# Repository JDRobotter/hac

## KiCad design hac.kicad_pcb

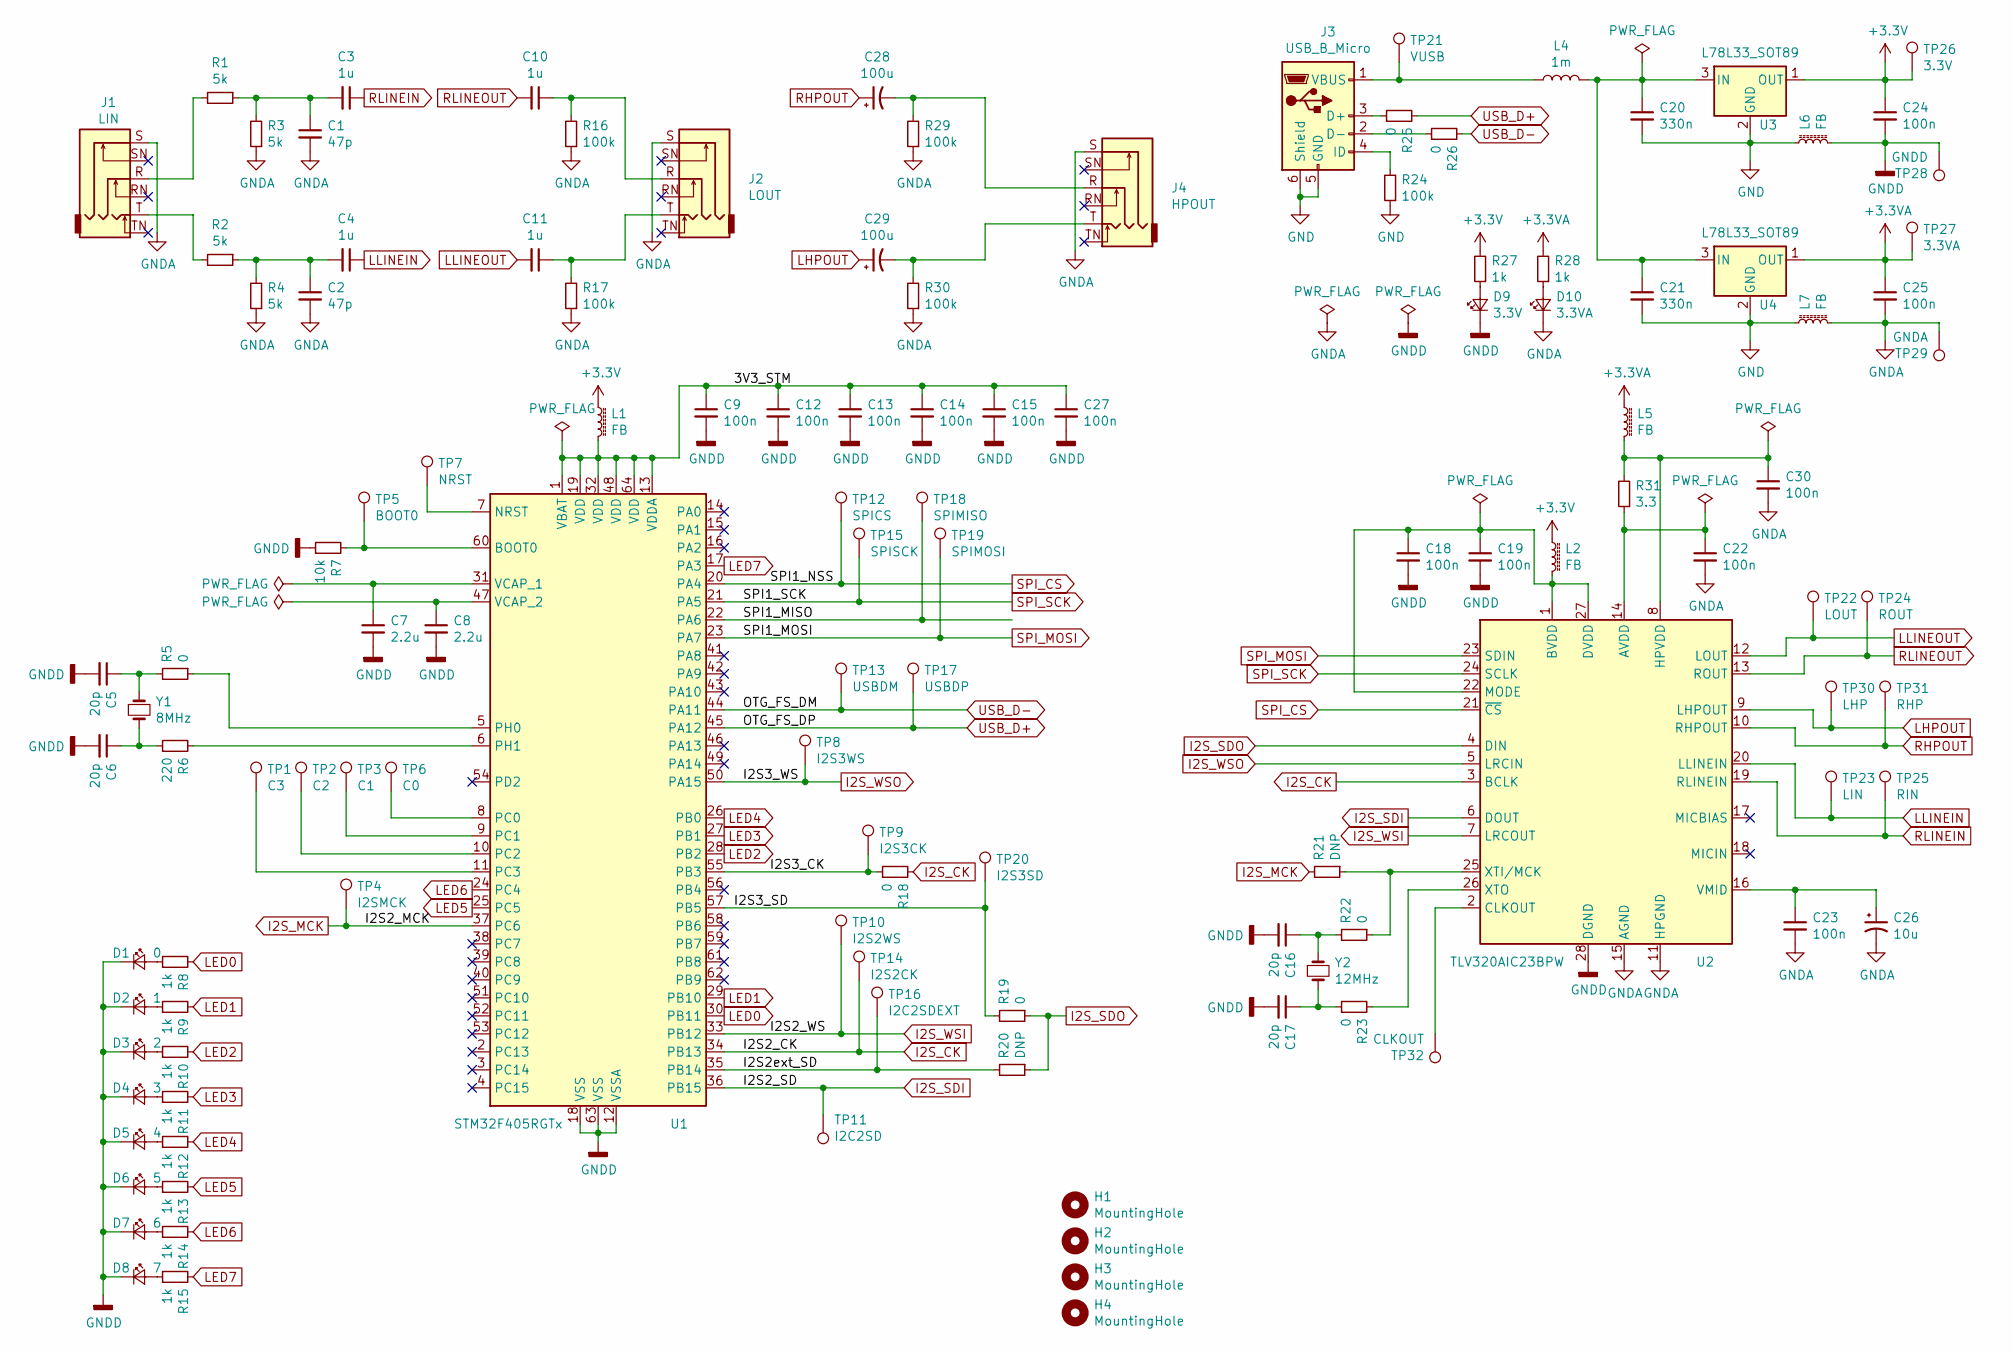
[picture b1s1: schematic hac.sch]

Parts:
C1, C2: 47p; C_0603_1608Metric
C3, C4, C10, C11: 1u; C_0805_2012Metric
C5, C6, C16, C17: 20p; C_0603_1608Metric
C7, C8: 2.2u; C_0805_2012Metric
C9, C12, C13, C14, C15, C18, C19, C22, C23, C24, C25, C27, C30: 100n; C_0603_1608Metric
C20, C21: 330n; C_0603_1608Metric
C26: 10u; CP_EIA-3216-18_Kemet-A
C28, C29: 100u; CP_EIA-6032-28_Kemet-C
D1: 0; LED_0603_1608Metric
D2: 1; LED_0603_1608Metric
D3: 2; LED_0603_1608Metric
D4: 3; LED_0603_1608Metric
D5: 4; LED_0603_1608Metric
D6: 5; LED_0603_1608Metric
D7: 6; LED_0603_1608Metric
D8: 7; LED_0603_1608Metric
D9: 3.3V; LED_0603_1608Metric
D10: 3.3VA; LED_0603_1608Metric
H1, H2, H3, H4: MountingHole; MountingHole_3.2mm_M3
J1: LIN; Jack_3.5mm_Neutrik_NMJ6HCD2_Horizontal
J2: LOUT; Jack_3.5mm_Neutrik_NMJ6HCD2_Horizontal
J3: USB_B_Micro; USB_Micro-B_Molex-105017-0001
J4: HPOUT; Jack_3.5mm_Neutrik_NMJ6HCD2_Horizontal
L1, L2, L5, L6, L7: FB; L_0805_2012Metric
L4: 1m; L_7.3x7.3_H4.5
R1, R2, R3, R4: 5k; R_0603_1608Metric
R5, R18, R19, R22, R23, R25, R26: 0; R_0603_1608Metric
R6: 220; R_0603_1608Metric
R7: 10k; R_0603_1608Metric
R8, R9, R10, R11, R12, R13, R14, R15, R27, R28: 1k; R_0603_1608Metric
R16, R17, R24, R29, R30: 100k; R_0603_1608Metric
R20, R21: DNP; R_0603_1608Metric
R31: 3.3; R_0603_1608Metric
TP1: C3; TestPoint_Pad_D1.5mm
TP2: C2; TestPoint_Pad_D1.5mm
TP3: C1; TestPoint_Pad_D1.5mm
TP4: I2SMCK; TestPoint_Pad_D1.5mm
TP5: BOOT0; TestPoint_Pad_D1.5mm
TP6: C0; TestPoint_Pad_D1.5mm
TP7: NRST; TestPoint_Pad_D1.5mm
TP8: I2S3WS; TestPoint_Pad_D1.5mm
TP9: I2S3CK; TestPoint_Pad_D1.5mm
TP10: I2S2WS; TestPoint_Pad_D1.5mm
TP11: I2C2SD; TestPoint_Pad_D1.5mm
TP12: SPICS; TestPoint_Pad_D1.5mm
TP13: USBDM; TestPoint_Pad_D1.5mm
TP14: I2S2CK; TestPoint_Pad_D1.5mm
TP15: SPISCK; TestPoint_Pad_D1.5mm
TP16: I2C2SDEXT; TestPoint_Pad_D1.5mm
TP17: USBDP; TestPoint_Pad_D1.5mm
TP18: SPIMISO; TestPoint_Pad_D1.5mm
TP19: SPIMOSI; TestPoint_Pad_D1.5mm
TP20: I2S3SD; TestPoint_Pad_D1.5mm
TP21: VUSB; TestPoint_Pad_D1.5mm
TP22: LOUT; TestPoint_Pad_D1.5mm
TP23: LIN; TestPoint_Pad_D1.5mm
TP24: ROUT; TestPoint_Pad_D1.5mm
TP25: RIN; TestPoint_Pad_D1.5mm
TP26: 3.3V; TestPoint_Pad_D1.5mm
TP27: 3.3VA; TestPoint_Pad_D1.5mm
TP28: GNDD; TestPoint_Pad_D1.5mm
TP29: GNDA; TestPoint_Pad_D1.5mm
TP30: LHP; TestPoint_Pad_D1.5mm
TP31: RHP; TestPoint_Pad_D1.5mm
TP32: CLKOUT; TestPoint_Pad_D1.5mm
U1: STM32F405RGTx; LQFP-64_10x10mm_P0.5mm
U2: TLV320AIC23BPW; TSSOP-28_4.4x9.7mm_P0.65mm
U3, U4: L78L33_SOT89; SOT-89-3
Y1: 8MHz; Crystal_SMD_HC49-SD
Y2: 12MHz; Crystal_SMD_HC49-SD

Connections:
+3.3VA: C25.1, L5.1, R28.2, TP27.1, U4.1 (OUT)
+3V3: C24.1, L1.1, L2.1, R27.2, TP26.1, U3.1 (OUT)
/3V3_STM: C9.1, C12.1, C13.1, C14.1, C15.1, C27.1, L1.2, U1.1 (VBAT), U1.13 (VDDA), U1.19 (VDD), U1.32 (VDD), U1.48 (VDD), U1.64 (VDD)
/I2S2ext_SD: R20.2, TP16.1, U1.35 (PB14)
/I2S3_CK: R18.1, TP9.1, U1.55 (PB3)
/I2S3_SD: R19.2, TP20.1, U1.57 (PB5)
/SPI1_MISO: TP18.1, U1.22 (PA6)
GND: C20.2, C21.2, J3.5 (GND), J3.6 (Shield), L6.1, L7.1, R24.1, U3.2 (GND), U4.2 (GND); also elsewhere on the board
GNDA: C1.2, C2.2, C22.2, C23.2, C25.2, C26.2, C30.2, D10.1 (K), J1.S, J2.S, J4.S, L7.2, R3.1, R4.1, R16.1, R17.1, R29.1, R30.1, TP29.1, U2.11 (HPGND), U2.15 (AGND); also elsewhere on the board
GNDD: C5.2, C6.2, C7.2, C8.2, C9.2, C12.2, C13.2, C14.2, C15.2, C16.2, C17.2, C18.2, C19.2, C24.2, C27.2, D1.1 (K), D2.1 (K), D3.1 (K), D4.1 (K), D5.1 (K), D6.1 (K), D7.1 (K), D8.1 (K), D9.1 (K), L6.2, R7.1, TP28.1, U1.12 (VSSA), U1.18 (VSS), U1.63 (VSS), U2.28 (DGND); also elsewhere on the board
I2S_CK: R18.2, TP14.1, U1.34 (PB13), U2.3 (BCLK)
I2S_MCK: R21.2, TP4.1, U1.37 (PC6)
I2S_SDI: TP11.1, U1.36 (PB15), U2.6 (DOUT)
I2S_SDO: R19.1, R20.1, U2.4 (DIN)
I2S_WSI: TP10.1, U1.33 (PB12), U2.7 (LRCOUT)
I2S_WSO: TP8.1, U1.50 (PA15), U2.5 (LRCIN)
LED0: R8.2, U1.30 (PB11)
LED1: R9.2, U1.29 (PB10)
LED2: R10.2, U1.28 (PB2)
LED3: R11.2, U1.27 (PB1)
LED4: R12.2, U1.26 (PB0)
LED5: R13.2, U1.25 (PC5)
LED6: R14.2, U1.24 (PC4)
LED7: R15.2, U1.17 (PA3)
LHPOUT: C29.1, TP30.1, U2.9 (LHPOUT)
LLINEIN: C4.1, TP23.1, U2.20 (LLINEIN)
LLINEOUT: C11.2, TP22.1, U2.12 (LOUT)
unnamed: C1.1, C3.2, R1.1, R3.2
unnamed: C2.1, C4.2, R2.1, R4.2
unnamed: C5.1, R5.2, Y1.1
unnamed: C6.1, R6.1, Y1.2
unnamed: C7.1, U1.31 (VCAP_1)
unnamed: C8.1, U1.47 (VCAP_2)
unnamed: C10.1, J2.R, R16.2
unnamed: C11.1, J2.T, R17.2
unnamed: C16.1, R22.2, Y2.1
unnamed: C17.1, R23.1, Y2.2
unnamed: C18.1, C19.1, L2.2, U2.1 (BVDD), U2.22 (MODE), U2.27 (DVDD)
unnamed: C20.1, C21.1, L4.2, U3.3 (IN), U4.3 (IN)
unnamed: C22.1, R31.1, U2.14 (AVDD)
unnamed: C23.1, C26.1, U2.16 (VMID)
unnamed: C28.2, J4.R, R29.2
unnamed: C29.2, J4.T, R30.2
unnamed: C30.1, L5.2, R31.2, U2.8 (HPVDD)
unnamed: D1.2 (A), R8.1
unnamed: D2.2 (A), R9.1
unnamed: D3.2 (A), R10.1
unnamed: D4.2 (A), R11.1
unnamed: D5.2 (A), R12.1
unnamed: D6.2 (A), R13.1
unnamed: D7.2 (A), R14.1
unnamed: D8.2 (A), R15.1
unnamed: D9.2 (A), R27.1
unnamed: D10.2 (A), R28.1
unnamed: J1.R, R1.2
unnamed: J1.T, R2.2
unnamed: J3.1 (VBUS), L4.1, TP21.1
unnamed: J3.2 (D-), R26.1
unnamed: J3.3 (D+), R25.1
unnamed: J3.4 (ID), R24.2
unnamed: R5.1, U1.5 (PH0)
unnamed: R6.2, U1.6 (PH1)
unnamed: R7.2, TP5.1, U1.60 (BOOT0)
unnamed: R21.1, R22.1, U2.25 (XTI/MCK)
unnamed: R23.2, U2.26 (XTO)
unnamed: TP1.1, U1.11 (PC3)
unnamed: TP2.1, U1.10 (PC2)
unnamed: TP3.1, U1.9 (PC1)
unnamed: TP6.1, U1.8 (PC0)
unnamed: TP7.1, U1.7 (NRST)
unnamed: TP32.1, U2.2 (CLKOUT)
RHPOUT: C28.1, TP31.1, U2.10 (RHPOUT)
RLINEIN: C3.1, TP25.1, U2.19 (RLINEIN)
RLINEOUT: C10.2, TP24.1, U2.13 (ROUT)
SPI_CS: TP12.1, U1.20 (PA4), U2.21 (~CS~)
SPI_MOSI: TP19.1, U1.23 (PA7), U2.23 (SDIN)
SPI_SCK: TP15.1, U1.21 (PA5), U2.24 (SCLK)
USB_D+: R25.2, TP17.1, U1.45 (PA12)
USB_D-: R26.2, TP13.1, U1.44 (PA11)

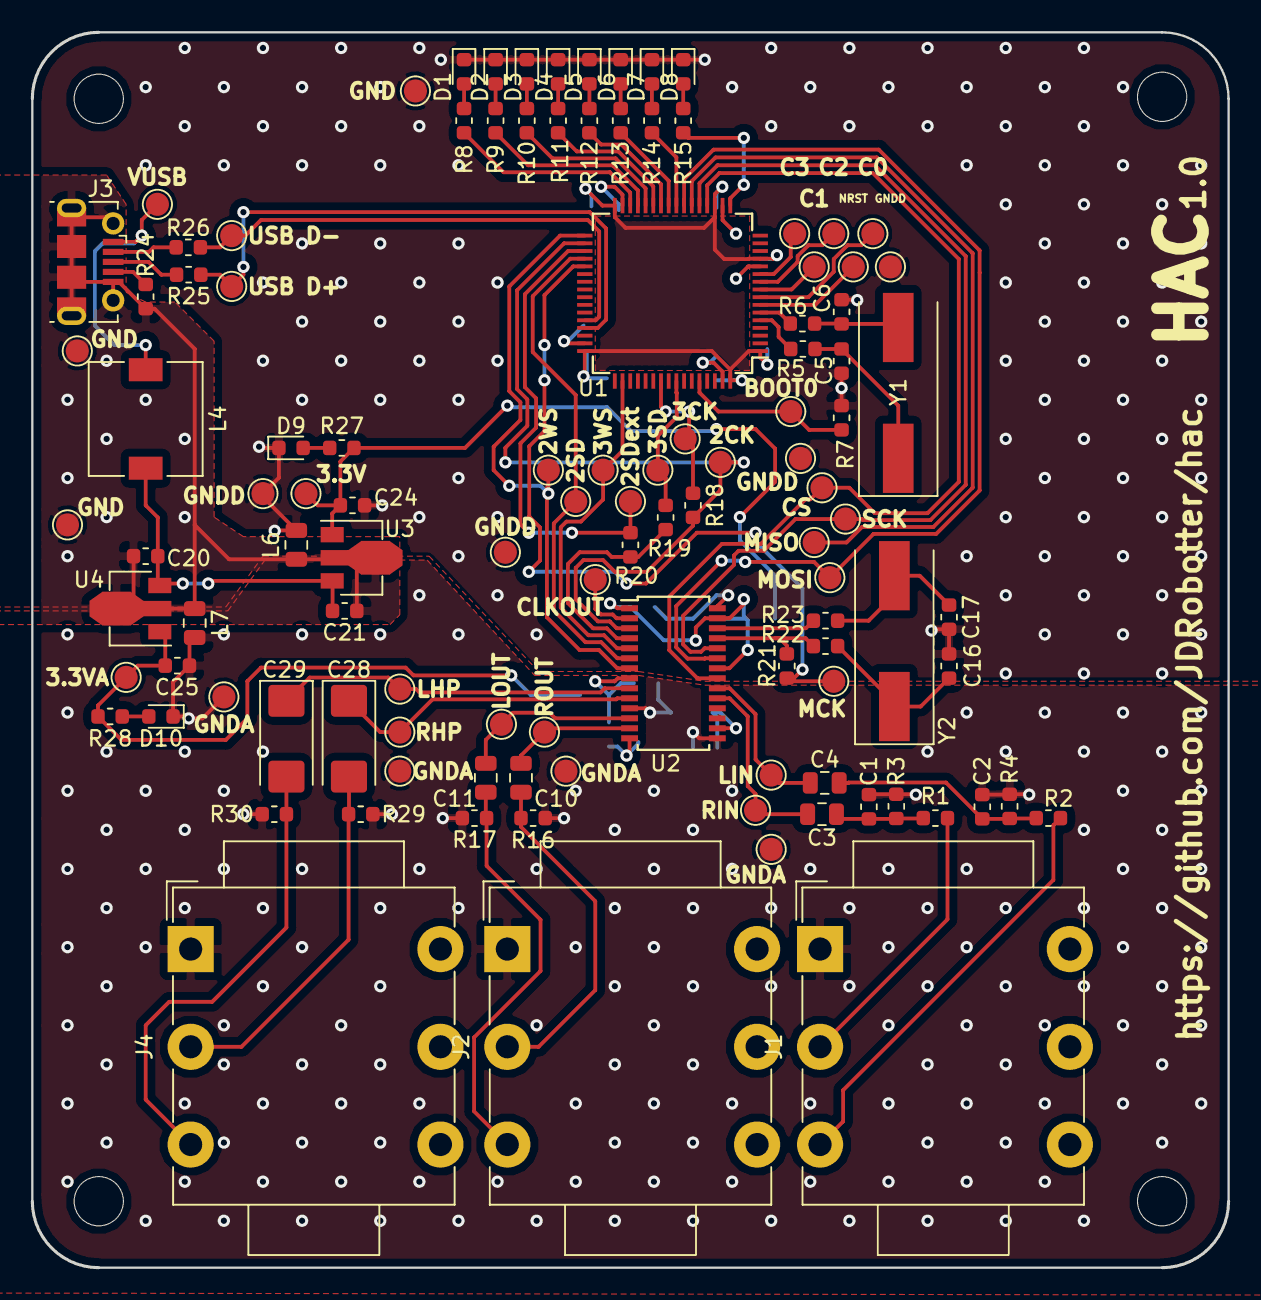
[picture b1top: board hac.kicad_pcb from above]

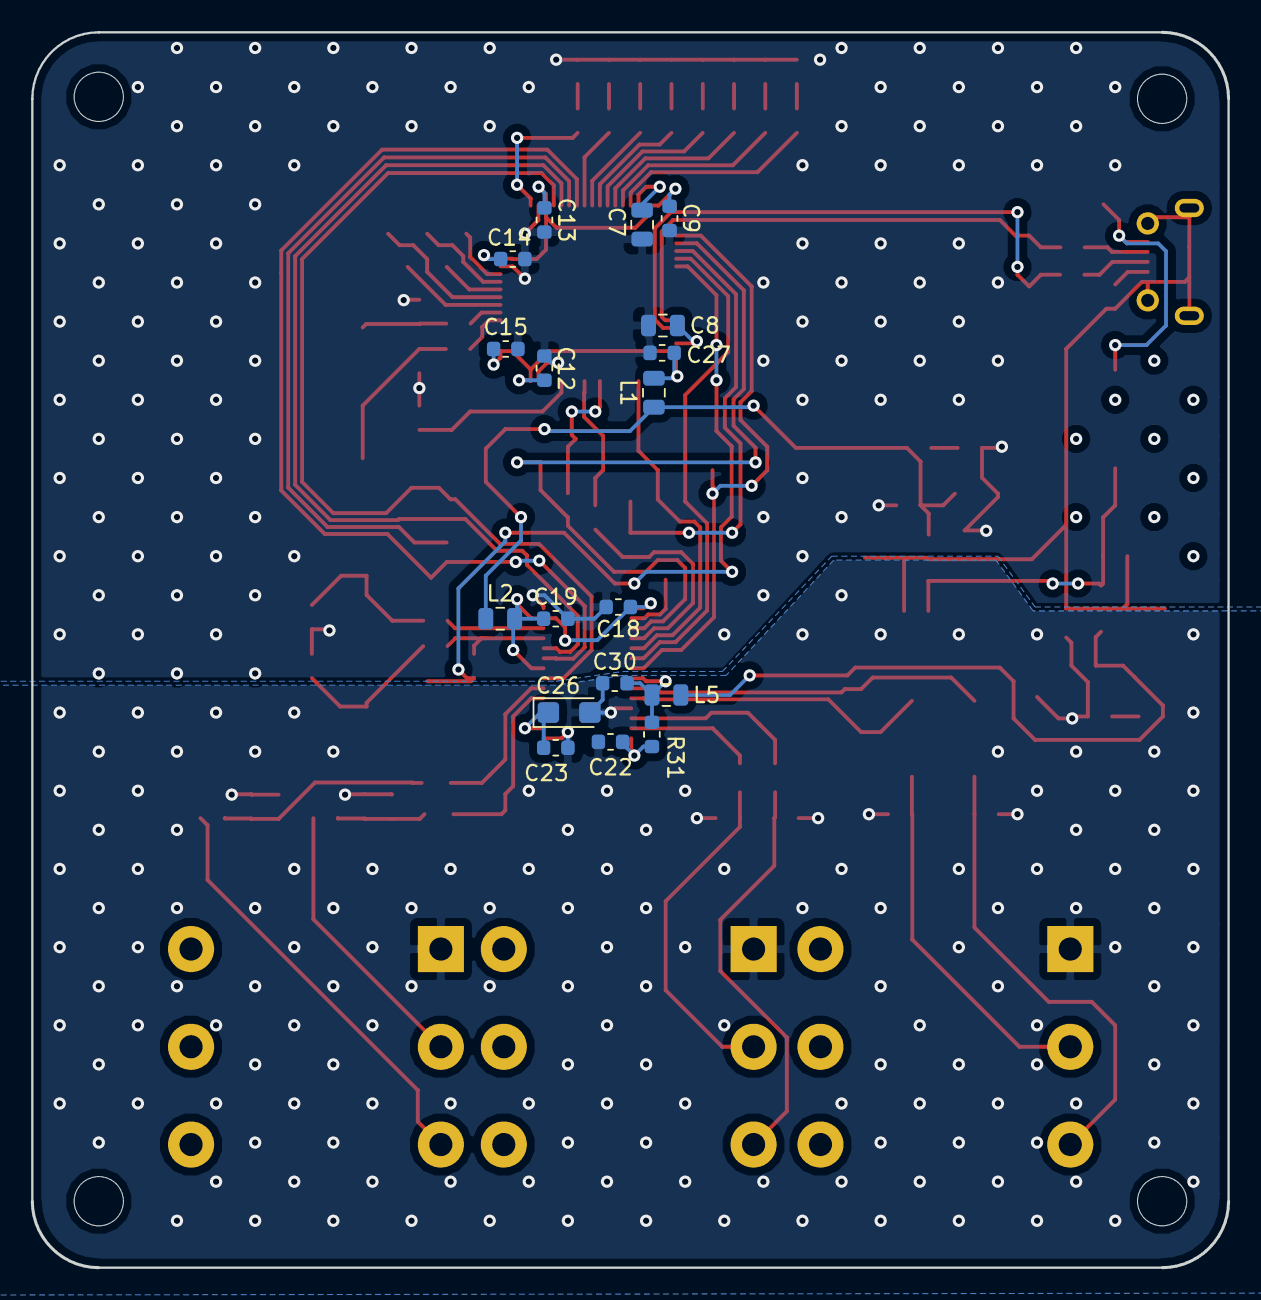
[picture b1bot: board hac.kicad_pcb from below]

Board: 2 copper layers, 77.7 x 80.3 mm, 132 parts (18 on the bottom side), 79 nets.

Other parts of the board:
TP33, TP34: GND; TestPoint_Pad_D1.5mm
TP35, TP37, TP39, TP41: GNDD; TestPoint_Pad_D1.5mm
TP36, TP38, TP40: GNDA; TestPoint_Pad_D1.5mm

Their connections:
GND: TP33.1, TP34.1; also elsewhere on the board
GNDA: TP36.1, TP38.1, TP40.1; also elsewhere on the board
GNDD: TP35.1, TP37.1, TP39.1, TP41.1; also elsewhere on the board

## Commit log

2019-01-20 schm done
2019-01-20 schm fixes + footprints done
2019-01-21 component placement done
2019-01-21 routing almost done
2019-01-21 some routing done
2019-02-01 gerbers + fixes
